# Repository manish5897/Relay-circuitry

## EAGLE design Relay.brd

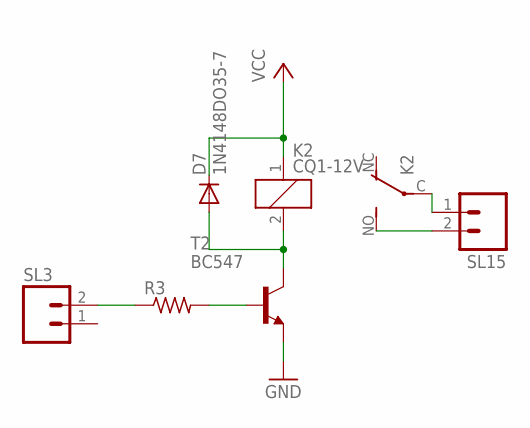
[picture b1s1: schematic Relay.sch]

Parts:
D7: 1N4148DO35-7; DO35-7
K2: CQ1-12V; CQ1
R3: R-US_0204/7; 0204/7
SL3, SL15: M02; 02P
T2: BC547; TO92

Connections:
GND: T2.1 (E)
unnamed: D7.A, K2.2, T2.3 (C)
unnamed: R3.2, T2.2 (B)
unnamed: K2.NO (S), SL15.2
unnamed: K2.C, SL15.1
unnamed: R3.1, SL3.2
VCC: D7.C, K2.1

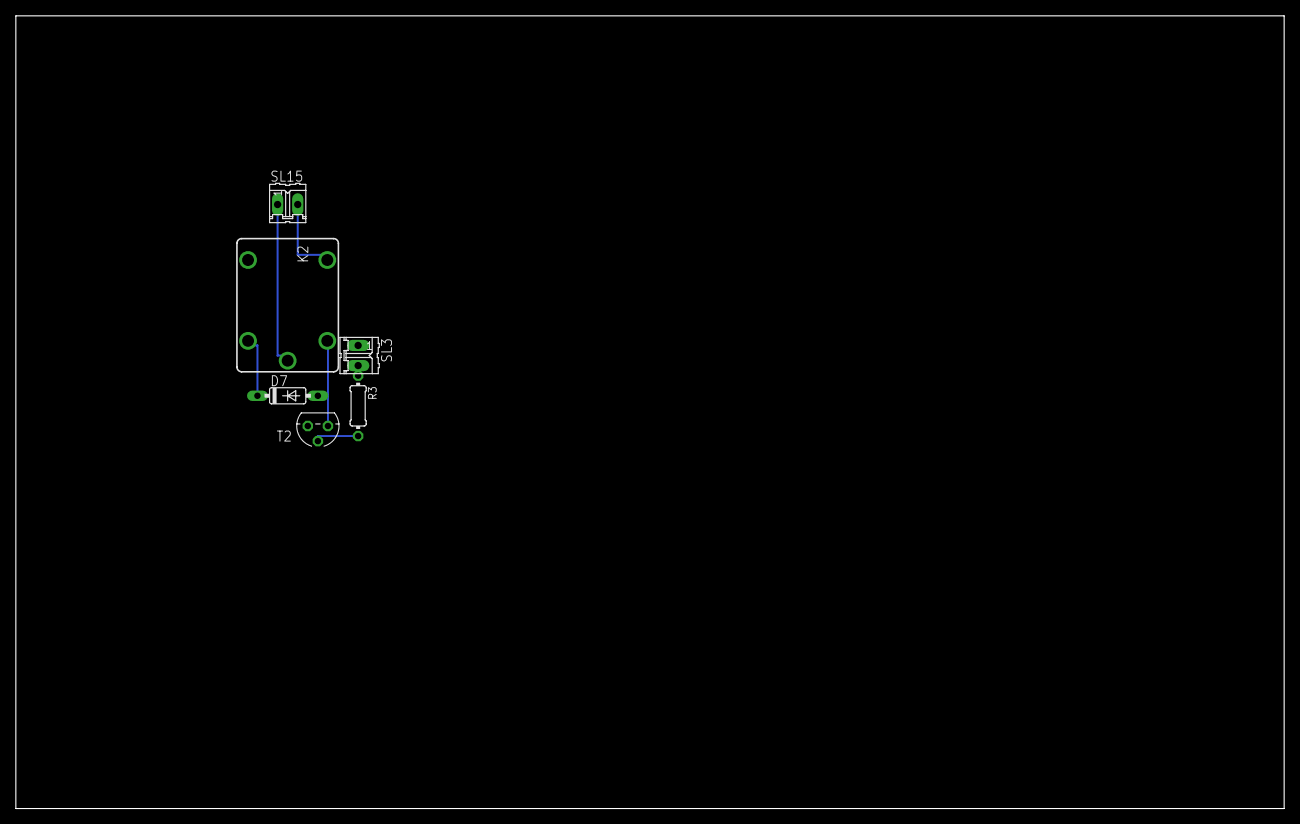
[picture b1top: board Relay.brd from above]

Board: 2 copper layers, 160.0 x 100.0 mm, 6 parts (0 on the bottom side), 6 nets.

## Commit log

2018-08-13 Relay circuitry in eagle cadsoft
